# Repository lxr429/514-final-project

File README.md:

# 514-final-project
## Part 1

## Part 2 - Sensor Device

## Part 3 - Display Device

## Part 4

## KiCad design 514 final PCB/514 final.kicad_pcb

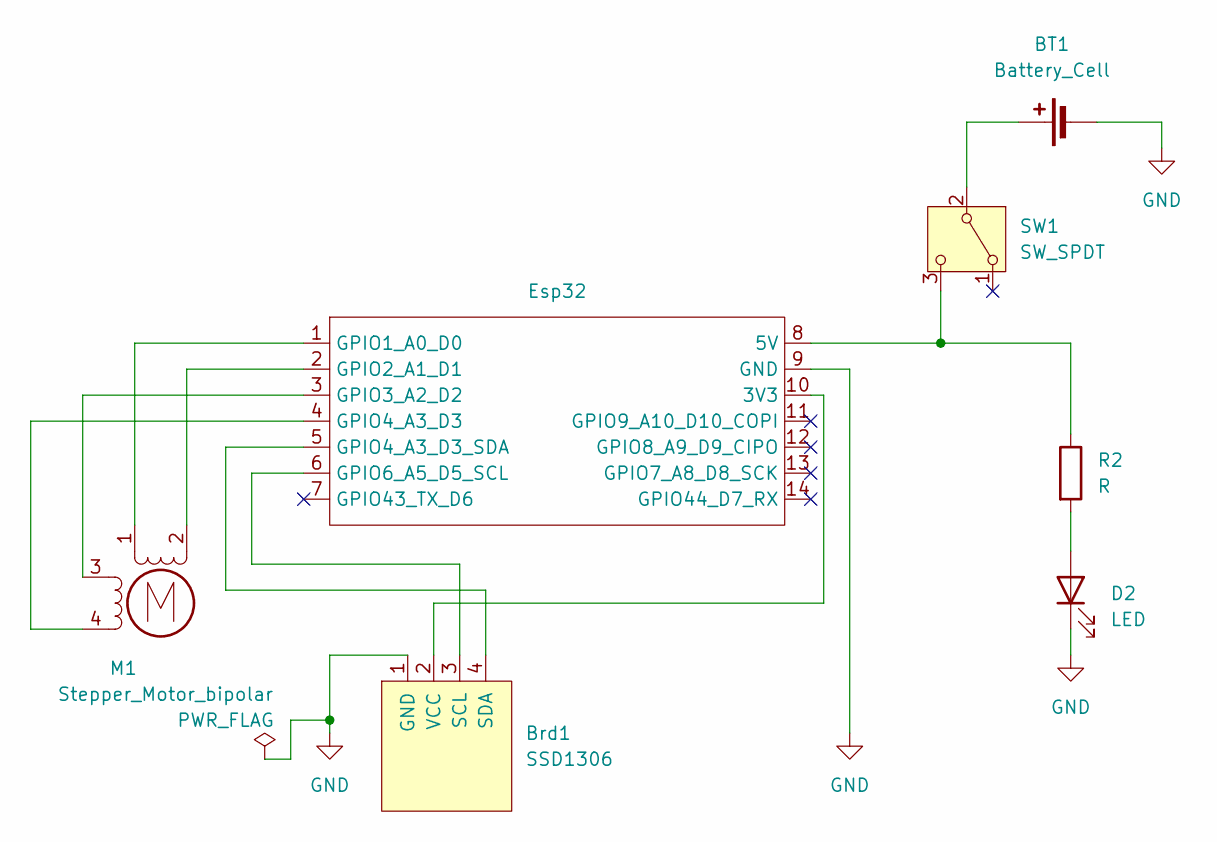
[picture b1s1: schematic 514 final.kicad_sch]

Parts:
BT1: Battery_Cell; JST_NV_B02P-NV_1x02_P5.00mm_Vertical
Brd1: SSD1306; 128x64OLED
D2: LED; LED_0805_2012Metric_Pad1.15x1.40mm_HandSolder
Esp32: XIAO_ESP32_SENSE
M1: Stepper_Motor_bipolar; x27_stepper
R2: R; R_0805_2012Metric_Pad1.20x1.40mm_HandSolder
SW1: SW_SPDT; JST_EH_B3B-EH-A_1x03_P2.50mm_Vertical

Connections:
GND: BT1.2 (-), Brd1.1 (GND), D2.1 (K), Esp32.9 (GND)
unnamed: BT1.1 (+), SW1.2 (B)
unnamed: Brd1.3 (SCL), Esp32.6 (GPIO6_A5_D5_SCL)
unnamed: Brd1.4 (SDA), Esp32.5 (GPIO4_A3_D3_SDA)
unnamed: Brd1.2 (VCC), Esp32.10 (3V3)
unnamed: D2.2 (A), R2.2
unnamed: Esp32.8 (5V), R2.1, SW1.3 (C)
unnamed: Esp32.1 (GPIO1_A0_D0), M1.1
unnamed: Esp32.2 (GPIO2_A1_D1), M1.2 (-)
unnamed: Esp32.3 (GPIO3_A2_D2), M1.3
unnamed: Esp32.4 (GPIO4_A3_D3), M1.4

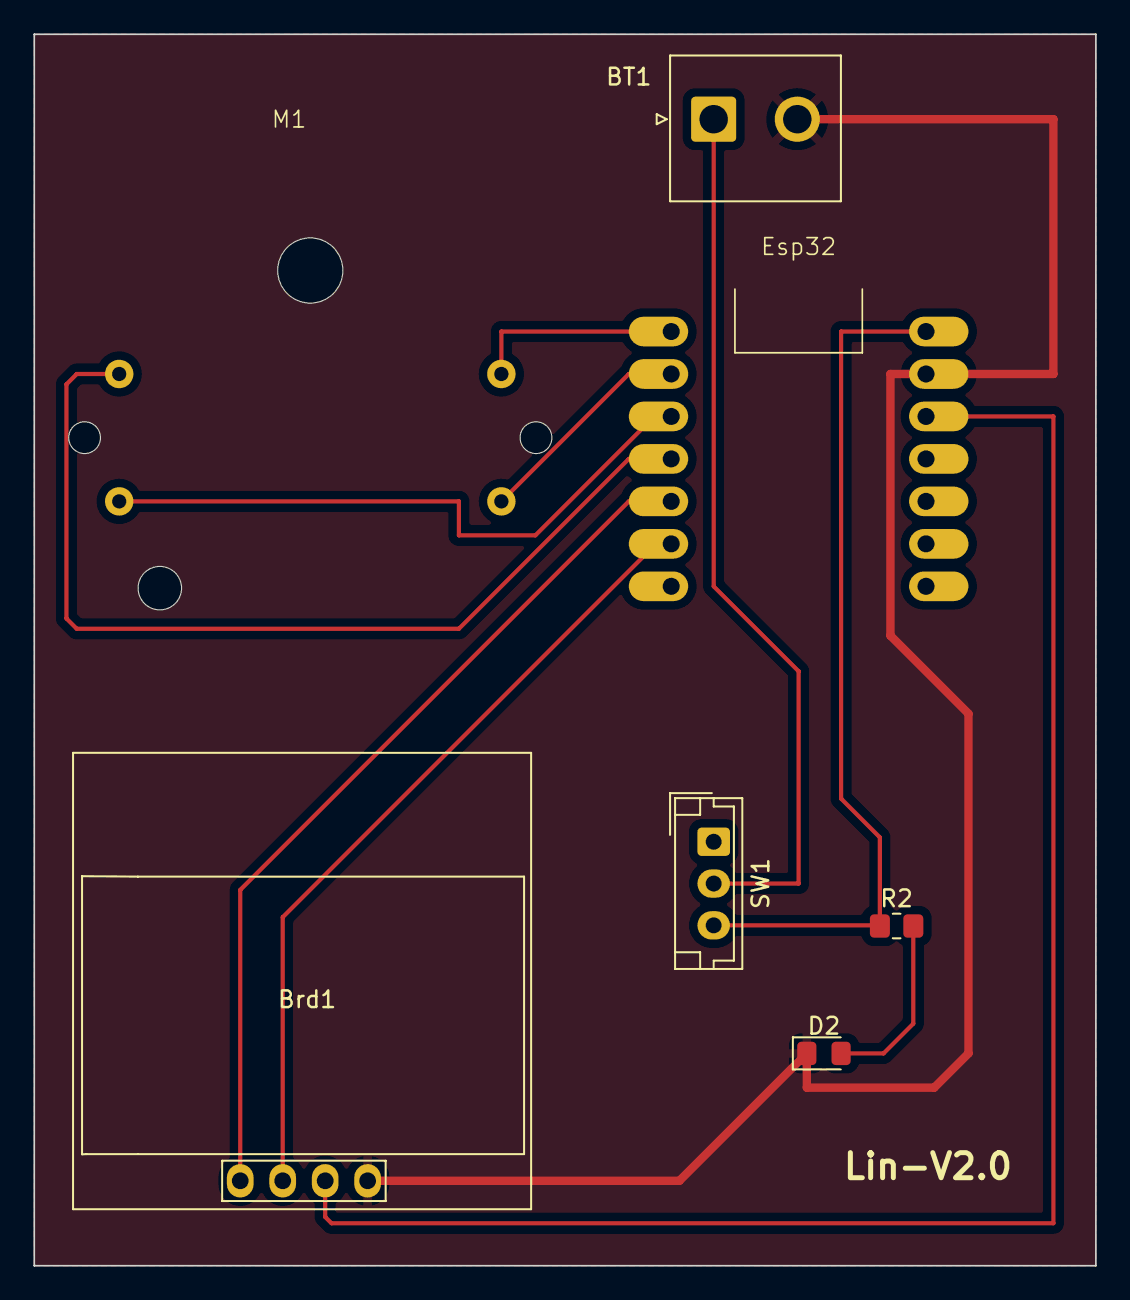
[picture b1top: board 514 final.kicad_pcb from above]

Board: 2 copper layers, 63.5 x 73.7 mm, 7 parts (0 on the bottom side), 11 nets.

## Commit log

2024-01-17 Update README.md
    12
